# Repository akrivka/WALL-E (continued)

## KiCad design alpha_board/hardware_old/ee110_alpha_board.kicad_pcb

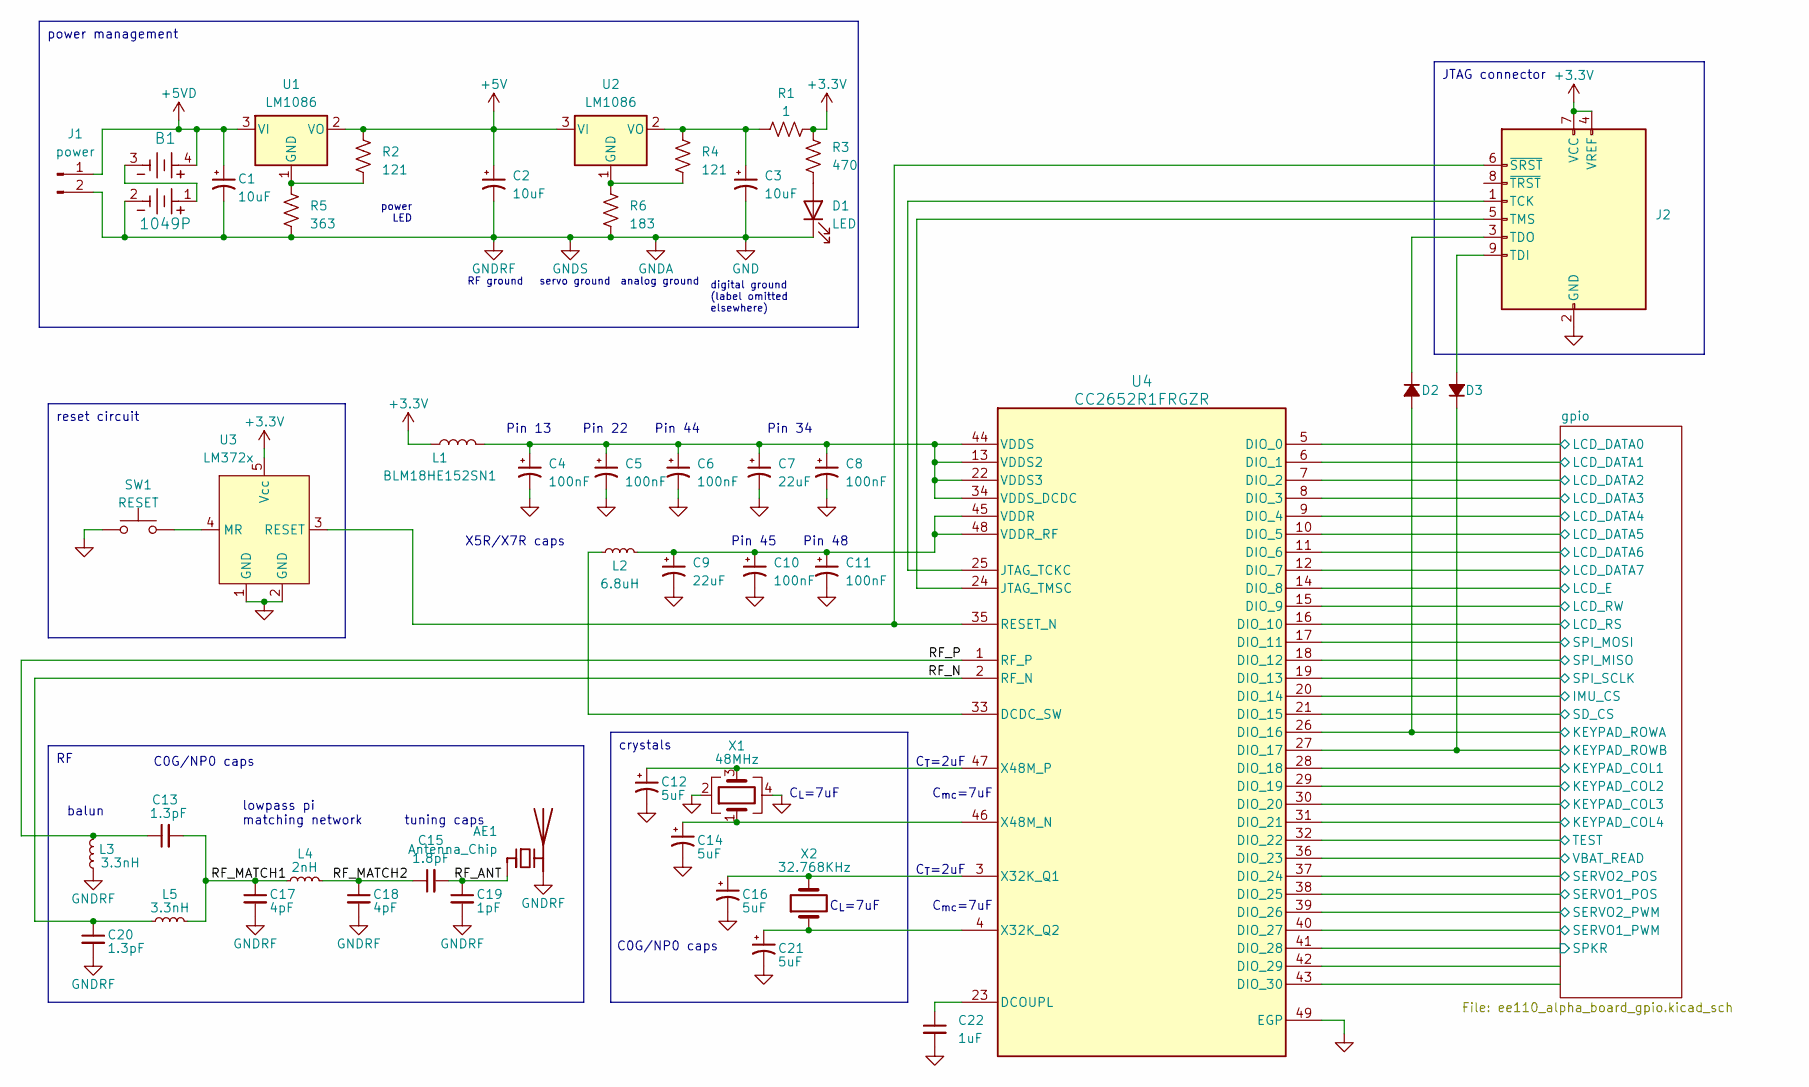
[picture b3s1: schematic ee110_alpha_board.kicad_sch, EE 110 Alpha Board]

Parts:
AE1: Antenna_Chip; EE110_Antenna
B1: 1049P; 1049P_KEY
C1, C2, C3: 10uF; CP_EIA-1608-08_AVX-J
C4, C5, C6, C8, C10, C11: 100nF; CP_EIA-1608-08_AVX-J
C7, C9: 22uF; CP_EIA-1608-08_AVX-J
C12, C14, C16, C21: 5uF; CP_EIA-1608-08_AVX-J
C13, C20: 1.3pF; C_1206_3216Metric
C15: 1.8pF; C_1206_3216Metric
C17, C18: 4pF; C_1206_3216Metric
C19: 1pF; C_1206_3216Metric
C22: 1uF; C_0603_1608Metric
D1: LED; LED_D3.0mm
D2, D3: D_Small_Filled; D_0603_1608Metric
J1: power; My_Power_Connector
J2: AVR-JTAG-10; CON10_2X5_DUK_FTSH_SAI
L1: BLM18HE152SN1; L_7.3x7.3_H3.5
L2: 6.8uH; L_0603_1608Metric
L3, L5: 3.3nH; L_1206_3216Metric
L4: 2nH; L_1206_3216Metric
R1: 1; R_0603_1608Metric
R2, R4: 121; R_0603_1608Metric
R3: 470; R_0603_1608Metric
R5: 363; R_0603_1608Metric
R6: 183; R_0603_1608Metric
SW1: RESET; SW_PUSH_6mm
U1, U2: LM1086; TO-263-3_TabPin2
U3: LM372x; SOT-23-5
U4: CC2652R1FRGZR; RGZ0048A_NV
X1: 48MHz; Crystal_SMD_2016-4Pin_2.0x1.6mm
X2: 32.768KHz; Crystal_SMD_3215-2Pin_3.2x1.5mm

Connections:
+3.3V: J2.4 (VREF), J2.7 (VCC), L1.1, R1.2, R3.1, U3.5 (Vcc); also elsewhere on the board
+5V: C2.1, R2.1, U1.2 (VO), U2.3 (VI); also elsewhere on the board
+5VD: B1.4, C1.1, J1.1, U1.3 (VI); also elsewhere on the board
/RF_ANT: AE1.1 (FEED), C15.2, C19.1
/RF_MATCH1: C13.2, C17.1, L4.1, L5.2
/RF_MATCH2: C15.1, C18.1, L4.2
/RF_N: C20.1, L5.1, U4.2 (RF_N)
/RF_P: C13.1, L3.2, U4.1 (RF_P)
/gpio/IMU_CS: U4.20 (DIO_14); also elsewhere on the board
/gpio/KEYPAD_COL1: U4.28 (DIO_18); also elsewhere on the board
/gpio/KEYPAD_COL2: U4.29 (DIO_19); also elsewhere on the board
/gpio/KEYPAD_COL3: U4.30 (DIO_20); also elsewhere on the board
/gpio/KEYPAD_COL4: U4.31 (DIO_21); also elsewhere on the board
/gpio/KEYPAD_ROWA: D2.2 (A), U4.26 (DIO_16); also elsewhere on the board
/gpio/KEYPAD_ROWB: D3.1 (K), U4.27 (DIO_17); also elsewhere on the board
/gpio/LCD_DATA0: U4.5 (DIO_0); also elsewhere on the board
/gpio/LCD_DATA1: U4.6 (DIO_1); also elsewhere on the board
/gpio/LCD_DATA2: U4.7 (DIO_2); also elsewhere on the board
/gpio/LCD_DATA3: U4.8 (DIO_3); also elsewhere on the board
/gpio/LCD_DATA4: U4.9 (DIO_4); also elsewhere on the board
/gpio/LCD_DATA5: U4.10 (DIO_5); also elsewhere on the board
/gpio/LCD_DATA6: U4.11 (DIO_6); also elsewhere on the board
/gpio/LCD_DATA7: U4.12 (DIO_7); also elsewhere on the board
/gpio/LCD_E: U4.14 (DIO_8); also elsewhere on the board
/gpio/LCD_RS: U4.16 (DIO_10); also elsewhere on the board
/gpio/LCD_RW: U4.15 (DIO_9); also elsewhere on the board
/gpio/SD_CS: U4.21 (DIO_15); also elsewhere on the board
/gpio/SERVO1_POS: U4.38 (DIO_25); also elsewhere on the board
/gpio/SERVO1_PWM: U4.40 (DIO_27); also elsewhere on the board
/gpio/SERVO2_POS: U4.37 (DIO_24); also elsewhere on the board
/gpio/SERVO2_PWM: U4.39 (DIO_26); also elsewhere on the board
/gpio/SPI_MISO: U4.18 (DIO_12); also elsewhere on the board
/gpio/SPI_MOSI: U4.17 (DIO_11); also elsewhere on the board
/gpio/SPI_SCLK: U4.19 (DIO_13); also elsewhere on the board
/gpio/SPKR: U4.41 (DIO_28); also elsewhere on the board
/gpio/TEST: U4.32 (DIO_22); also elsewhere on the board
/gpio/VBAT_READ: U4.36 (DIO_23); also elsewhere on the board
GND: AE1.2 (PCB_Trace), B1.2, C1.2, C2.2, C3.2, C4.2, C5.2, C6.2, C7.2, C8.2, C9.2, C10.2, C11.2, C12.2, C14.2, C16.2, C17.2, C18.2, C19.2, C20.2, C21.2, C22.2, D1.1 (K), J1.2, J2.2 (GND), J2.10 (GND), L3.1, R5.2, R6.2, SW1.1, U3.1 (GND), U3.2 (GND), U4.49 (EGP), X1.2, X1.4; also elsewhere on the board
unnamed: B1.1, B1.3
unnamed: D1.2 (A), R3.2
unnamed: D2.1 (K), J2.3 (TDO)
unnamed: D3.2 (A), J2.9 (TDI)
unnamed: J2.1 (TCK), U4.25 (JTAG_TCKC)
unnamed: J2.5 (TMS), U4.24 (JTAG_TMSC)
unnamed: J2.6 (~SRST), U3.3 (RESET), U4.35 (RESET_N)
unnamed: R2.2, R5.1, U1.1 (GND)
unnamed: R4.2, R6.1, U2.1 (GND)
unnamed: C3.1, R1.1, R4.1, U2.2 (VO)
unnamed: SW1.2, U3.4 (MR)
unnamed: L2.1, U4.33 (DCDC_SW)
unnamed: C22.1, U4.23 (DCOUPL)
unnamed: C9.1, C10.1, C11.1, L2.2, U4.45 (VDDR), U4.48 (VDDR_RF)
unnamed: C4.1, C5.1, C6.1, C7.1, C8.1, L1.2, U4.13 (VDDS2), U4.22 (VDDS3), U4.34 (VDDS_DCDC), U4.44 (VDDS)
unnamed: C16.1, U4.3 (X32K_Q1), X2.2
unnamed: C21.1, U4.4 (X32K_Q2), X2.1
unnamed: C14.1, U4.46 (X48M_N), X1.1
unnamed: C12.1, U4.47 (X48M_P), X1.3

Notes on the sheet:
reset circuit
power management
JTAG connector
crystals
Pin 22
power LED
C_{mc}=7uF
tuning caps
Pin 44
lowpass pi matching network
C0G/NP0 caps
X5R/X7R caps
C_{T}=2uF
RF ground
Pin 48
Pin 45
C_{L}=7uF
Pin 34
servo ground
analog ground
digital ground (label omitted elsewhere)
Pin 13
balun

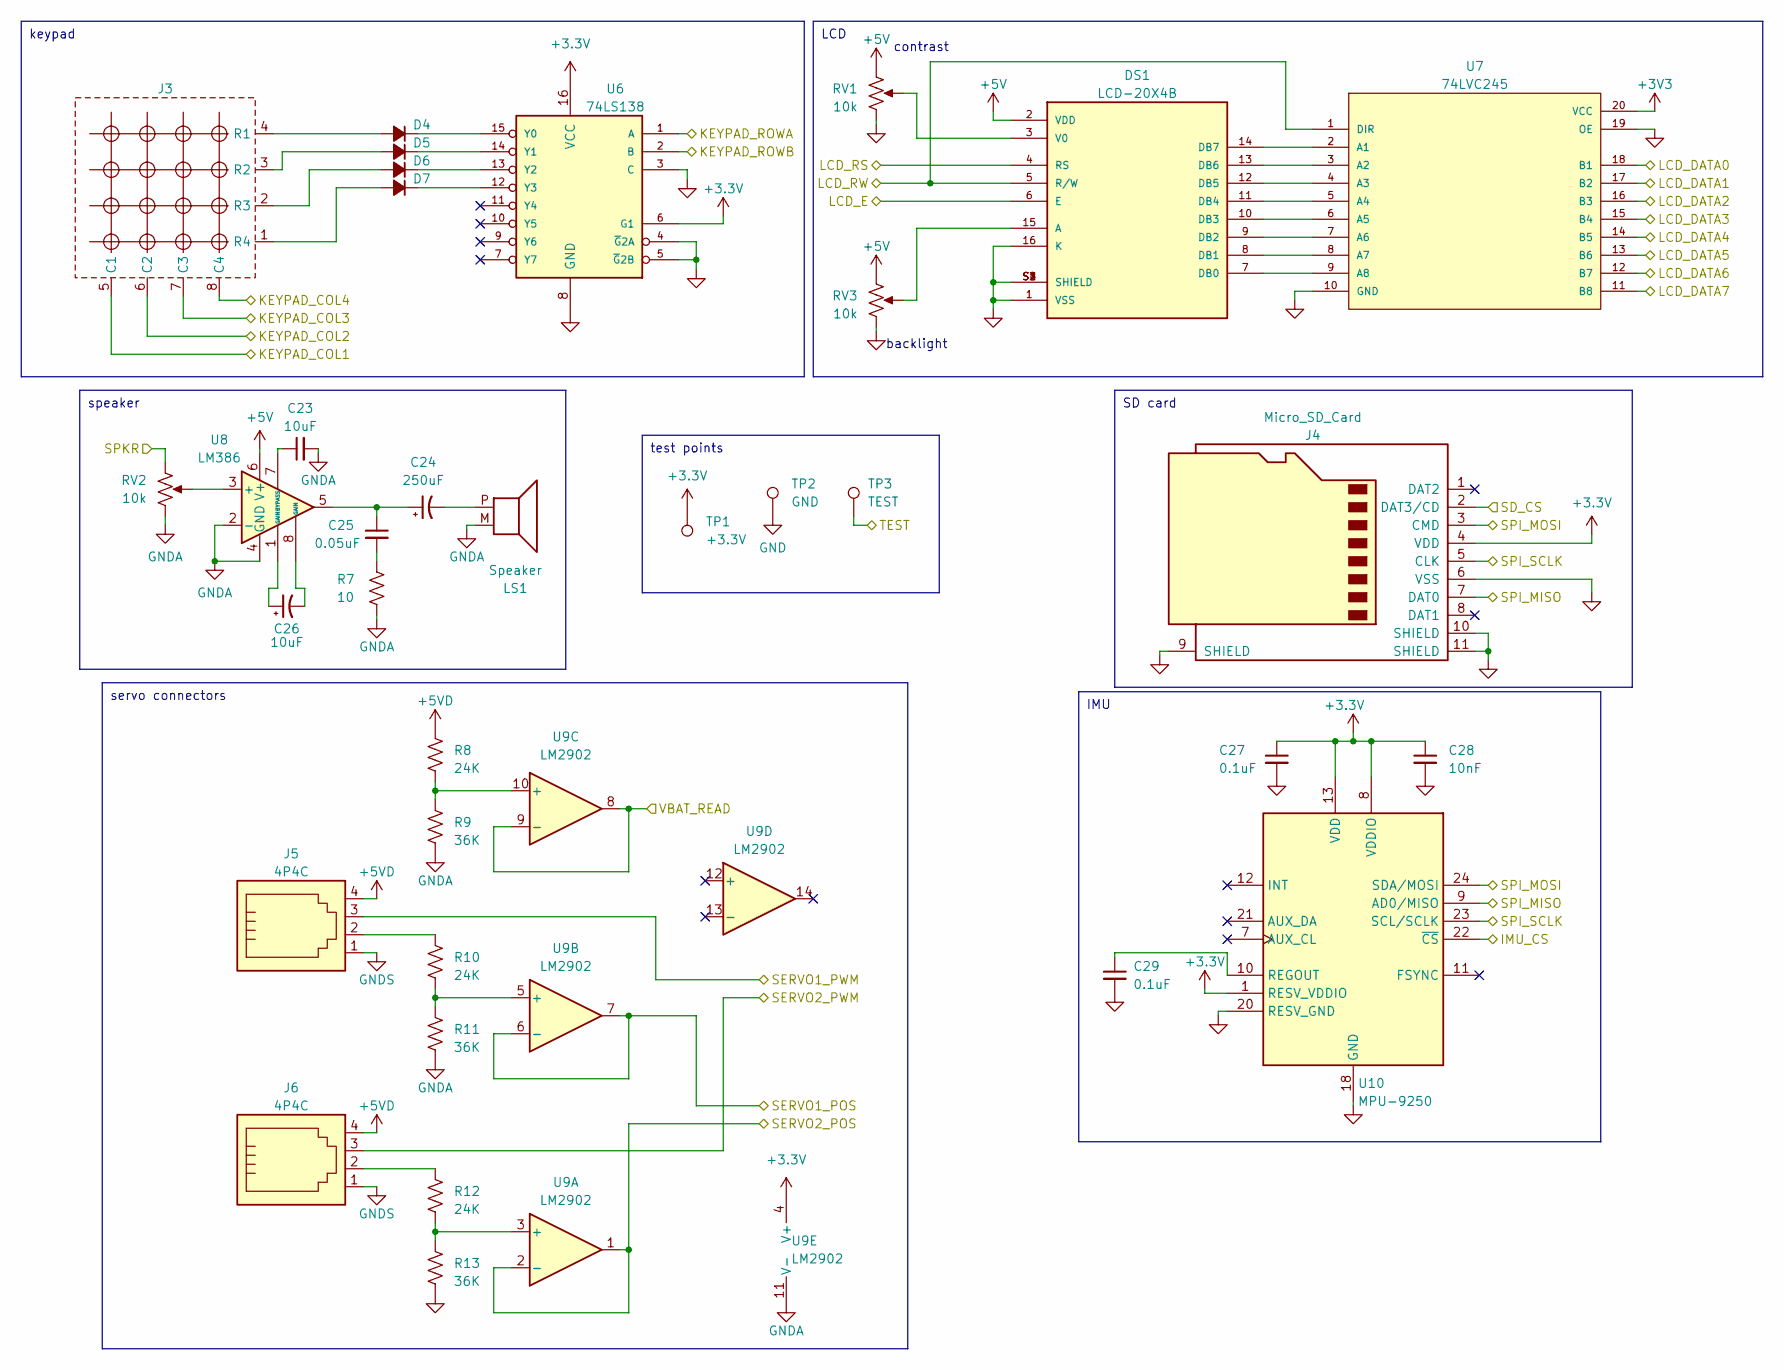
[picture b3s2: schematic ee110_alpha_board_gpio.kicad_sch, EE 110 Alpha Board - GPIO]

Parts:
C23, C26: 10uF; C_0603_1608Metric
C24: 250uF; C_0603_1608Metric
C25: 0.05uF; C_0603_1608Metric
C27, C29: 0.1uF; C_0603_1608Metric
C28: 10nF; C_0603_1608Metric
D4, D5, D6, D7: D_Small_Filled; D_0603_1608Metric
DS1: LCD-20X4B; LCD_LCD-20X4B; PARTREV N/A
J3: 4x4_Keypad
J4: Micro_SD_Card; microSD_HC_Hirose_DM3D-SF
J5, J6: 4P4C; JST_XH_S4B-XH-A-1_1x04_P2.50mm_Horizontal
LS1: Speaker; SPKR_CVS-1508
R7: 10; R_0603_1608Metric
R8, R10, R12: 24K; R_0603_1608Metric
R9, R11, R13: 36K; R_0603_1608Metric
RV1, RV3: 10k; Potentiometer_Bourns_3296P_Horizontal
RV2: 10k; TRIM_PTV09A-2015U-B103
TP1: +3.3V; TestPoint_THTPad_2.0x2.0mm_Drill1.0mm
TP2: GND; TestPoint_THTPad_2.0x2.0mm_Drill1.0mm
TP3: TEST; TestPoint_THTPad_2.0x2.0mm_Drill1.0mm
U6: 74LS138; SOIC-16_3.9x9.9mm_P1.27mm
U7: 74LVC245; SOIC-20W_7.5x15.4mm_P1.27mm
U8: LM386; DIP-8_W7.62mm
U9: LM2902; SOIC-14_3.9x8.7mm_P1.27mm
U10: MPU-9250; InvenSense_QFN-24_3x3mm_P0.4mm

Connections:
+3.3V: C27.1, C28.1, J4.4 (VDD), TP1.1, U6.6 (G1), U6.16 (VCC), U9.4 (V+), U10.1 (RESV_VDDIO), U10.8 (VDDIO), U10.13 (VDD); also elsewhere on the board
+3V3: U7.20 (VCC)
+5V: DS1.2 (VDD), RV1.1, RV3.1, U8.6 (V+); also elsewhere on the board
+5VD: J5.4, J6.4, R8.1; also elsewhere on the board
/gpio/IMU_CS: U10.22 (~CS); also elsewhere on the board
/gpio/KEYPAD_COL1: J3.5 (C1); also elsewhere on the board
/gpio/KEYPAD_COL2: J3.6 (C2); also elsewhere on the board
/gpio/KEYPAD_COL3: J3.7 (C3); also elsewhere on the board
/gpio/KEYPAD_COL4: J3.8 (C4); also elsewhere on the board
/gpio/KEYPAD_ROWA: U6.1 (A); also elsewhere on the board
/gpio/KEYPAD_ROWB: U6.2 (B); also elsewhere on the board
/gpio/LCD_DATA0: U7.18 (B1); also elsewhere on the board
/gpio/LCD_DATA1: U7.17 (B2); also elsewhere on the board
/gpio/LCD_DATA2: U7.16 (B3); also elsewhere on the board
/gpio/LCD_DATA3: U7.15 (B4); also elsewhere on the board
/gpio/LCD_DATA4: U7.14 (B5); also elsewhere on the board
/gpio/LCD_DATA5: U7.13 (B6); also elsewhere on the board
/gpio/LCD_DATA6: U7.12 (B7); also elsewhere on the board
/gpio/LCD_DATA7: U7.11 (B8); also elsewhere on the board
/gpio/LCD_E: DS1.6 (E); also elsewhere on the board
/gpio/LCD_RS: DS1.4 (RS); also elsewhere on the board
/gpio/LCD_RW: DS1.5 (R/W), U7.1 (DIR); also elsewhere on the board
/gpio/SD_CS: J4.2 (DAT3/CD); also elsewhere on the board
/gpio/SERVO1_POS: U9.6 (-), U9.7; also elsewhere on the board
/gpio/SERVO1_PWM: J5.3; also elsewhere on the board
/gpio/SERVO2_POS: U9.1, U9.2 (-); also elsewhere on the board
/gpio/SERVO2_PWM: J6.3; also elsewhere on the board
/gpio/SPI_MISO: J4.7 (DAT0), U10.9 (AD0/MISO); also elsewhere on the board
/gpio/SPI_MOSI: J4.3 (CMD), U10.24 (SDA/MOSI); also elsewhere on the board
/gpio/SPI_SCLK: J4.5 (CLK), U10.23 (SCL/SCLK); also elsewhere on the board
/gpio/SPKR: RV2.1; also elsewhere on the board
/gpio/TEST: TP3.1; also elsewhere on the board
/gpio/VBAT_READ: U9.8, U9.9 (-); also elsewhere on the board
GND: C23.2, C27.2, C28.2, C29.2, DS1.1 (VSS), DS1.16 (K), DS1.S1 (SHIELD), DS1.S2 (SHIELD), DS1.S3 (SHIELD), DS1.S4 (SHIELD), J4.6 (VSS), J4.9 (SHIELD), J4.10 (SHIELD), J4.11 (SHIELD), J5.1, J6.1, LS1.M (2), R7.2, R9.2, R11.2, R13.2, RV1.3, RV2.3, RV3.3, TP2.1, U6.3 (C), U6.4 (~G2A), U6.5 (~G2B), U6.8 (GND), U7.10 (GND), U7.19 (OE), U8.2 (-), U8.4 (GND), U9.11 (V-), U10.18 (GND), U10.20 (RESV_GND); also elsewhere on the board
unnamed: C24.1, C25.1, U8.5
unnamed: C25.2, R7.1
unnamed: C26.1, U8.1 (GAIN)
unnamed: C26.2, U8.8 (GAIN)
unnamed: D4.2 (A), J3.4 (R1)
unnamed: D4.1 (K), U6.15 (Y0)
unnamed: D5.2 (A), J3.3 (R2)
unnamed: D5.1 (K), U6.14 (Y1)
unnamed: D6.2 (A), J3.2 (R3)
unnamed: D6.1 (K), U6.13 (Y2)
unnamed: D7.2 (A), J3.1 (R4)
unnamed: D7.1 (K), U6.12 (Y3)
unnamed: DS1.15 (A), RV3.2
unnamed: DS1.7 (DB0), U7.9 (A8)
unnamed: DS1.8 (DB1), U7.8 (A7)
unnamed: DS1.9 (DB2), U7.7 (A6)
unnamed: DS1.10 (DB3), U7.6 (A5)
unnamed: DS1.11 (DB4), U7.5 (A4)
unnamed: DS1.12 (DB5), U7.4 (A3)
unnamed: DS1.13 (DB6), U7.3 (A2)
unnamed: DS1.14 (DB7), U7.2 (A1)
unnamed: DS1.3 (V0), RV1.2
unnamed: J5.2, R10.1
unnamed: J6.2, R12.1
unnamed: C24.2, LS1.P (1)
unnamed: RV2.2, U8.3 (+)
unnamed: C23.1, U8.7 (BYPASS)
unnamed: R12.2, R13.1, U9.3 (+)
unnamed: R10.2, R11.1, U9.5 (+)
unnamed: R8.2, R9.1, U9.10 (+)
unnamed: C29.1, U10.10 (REGOUT)

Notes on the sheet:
test points
keypad
SD card
servo connectors
speaker
LCD
IMU
backlight
contrast

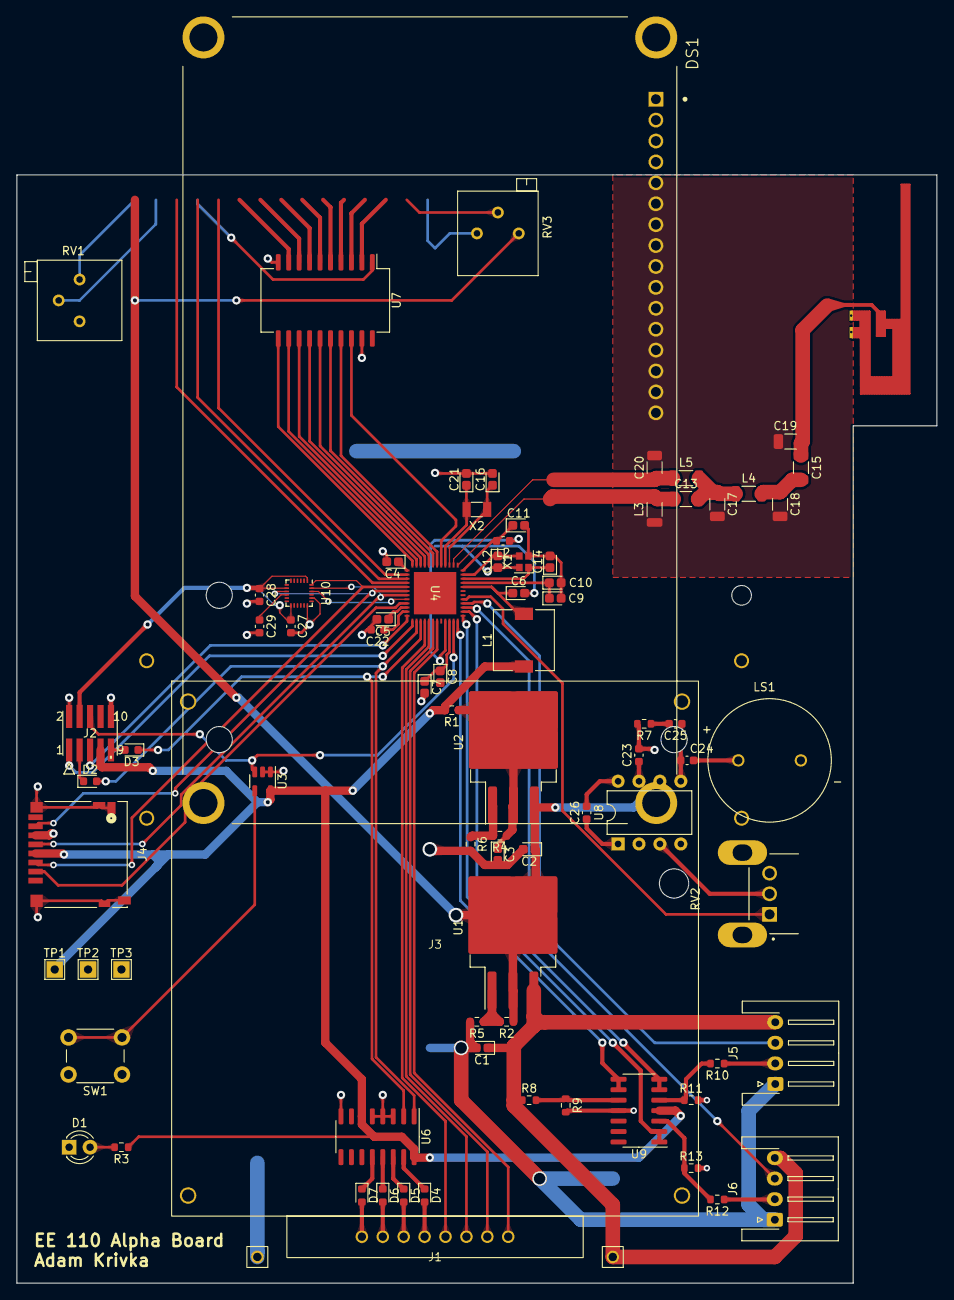
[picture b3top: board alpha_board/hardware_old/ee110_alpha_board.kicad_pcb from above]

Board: 2 copper layers, 111.8 x 134.6 mm, 82 parts (1 on the bottom side), 88 nets.

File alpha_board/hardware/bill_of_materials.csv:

"Id";"Designator";"Footprint";"Quantity";"Designation";"Supplier and ref";
1;"AE1";"EE110_Antenna";1;"Antenna_Chip";;;
2;"U8";"SOIC-14_3.9x8.7mm_P1.27mm";1;"LM2902";;;
3;"C17,C18";"C_1206_3216Metric_Pad1.33x1.80mm_HandSolder";2;"4pF";;;
4;"R10,R12,R14";"R_0603_1608Metric_Pad0.98x0.95mm_HandSolder";3;"24K";;;
5;"R15,R13,R11";"R_0603_1608Metric_Pad0.98x0.95mm_HandSolder";3;"36K";;;
6;"D10,D11";"D_1206_3216Metric_Pad1.42x1.75mm_HandSolder";2;"D_Small_Filled";;;
7;"C1,C3,C2";"CP_EIA-1608-08_AVX-J_Pad1.25x1.05mm_HandSolder";3;"10uF";;;
8;"C28";"C_0603_1608Metric_Pad1.08x0.95mm_HandSolder";1;"10nF";;;
9;"C12,C21,C16,C14";"CP_EIA-1608-08_AVX-J_Pad1.25x1.05mm_HandSolder";4;"5uF";;;
10;",,";"";3;"";;;
11;"C23,C26";"C_0603_1608Metric_Pad1.08x0.95mm_HandSolder";2;"10uF";;;
12;"U9";"QFN-24-1EP_3x3mm_P0.4mm_EP1.75x1.6mm";1;"MPU-9250";;;
13;"U6";"SOIC-20W_7.5x15.4mm_P1.27mm";1;"74LVC245";;;
14;"D7,D6,D4,D2,D5,D3";"D_0603_1608Metric_Pad1.05x0.95mm_HandSolder";6;"D_Small_Filled";;;
15;"C19";"C_1206_3216Metric_Pad1.33x1.80mm_HandSolder";1;"1pF";;;
16;"LS1";"SPKR_CVS-1508";1;"Speaker";;;
17;"C27,C29";"C_0603_1608Metric_Pad1.08x0.95mm_HandSolder";2;"0.1uF";;;
18;"D1";"LED_D3.0mm";1;"LED";;;
19;"C9,C7";"CP_EIA-1608-08_AVX-J_Pad1.25x1.05mm_HandSolder";2;"22uF";;;
20;"J3";"4x4_Keypad";1;"~";;;
21;"C15";"C_1206_3216Metric_Pad1.33x1.80mm_HandSolder";1;"1.8pF";;;
22;"RV2";"Potentiometer_Bourns_3296P_Horizontal";1;"1k";;;
23;"C4,C11,C8,C5,C10,C6";"CP_EIA-1608-08_AVX-J_Pad1.25x1.05mm_HandSolder";6;"100nF";;;
24;"J2";"CON10_2X5_DUK_FTSH_SAI";1;"AVR-JTAG-10";;;
25;"X1";"Crystal_SMD_2016-4Pin_2.0x1.6mm";1;"48MHz";;;
26;"R8,R4,R7";"R_0603_1608Metric_Pad0.98x0.95mm_HandSolder";3;"200";;;
27;"L5,L3";"L_1206_3216Metric_Pad1.22x1.90mm_HandSolder";2;"3.3nH";;;
28;"L2";"L_0603_1608Metric_Pad1.05x0.95mm_HandSolder";1;"6.8uH";;;
29;"RV3,RV1";"Potentiometer_Bourns_3296P_Horizontal";2;"10k";;;
30;"J6,J5";"JST_XH_S4B-XH-A-1_1x04_P2.50mm_Horizontal";2;"4P4C";;;
31;"L4";"L_1206_3216Metric_Pad1.22x1.90mm_HandSolder";1;"2nH";;;
32;"U2,U1";"TO-263-3_TabPin2";2;"LM1086";;;
33;"SW2";"SW_SPST_TL3342";1;"TEST_BUTTON";;;
34;"C24";"C_0603_1608Metric_Pad1.08x0.95mm_HandSolder";1;"250uF";;;
35;"U7";"DIP-8_W7.62mm";1;"LM386";;;
36;"TP1";"TestPoint_THTPad_2.0x2.0mm_Drill1.0mm";1;"TEST_BUTTON";;;
37;"TP2";"TestPoint_THTPad_2.0x2.0mm_Drill1.0mm";1;"TEST_GREEN";;;
38;"TP3";"TestPoint_THTPad_2.0x2.0mm_Drill1.0mm";1;"TEST_BLUE";;;
39;"R3,R2";"R_0603_1608Metric_Pad0.98x0.95mm_HandSolder";2;"121";;;
40;"SW1";"SW_SPST_TL3342";1;"RESET";;;
41;"DS1";"WINSTAR-WH1604A";1;"LCD-20X4B";;;
42;"TP5";"TestPoint_THTPad_2.0x2.0mm_Drill1.0mm";1;"GND";;;
43;"C25";"C_0603_1608Metric_Pad1.08x0.95mm_HandSolder";1;"0.05uF";;;
44;"TP4";"TestPoint_THTPad_2.0x2.0mm_Drill1.0mm";1;"+3.3V";;;
45;"U4";"RGZ0048A_NV";1;"CC2652R1FRGZR";;;
46;"R6";"R_0603_1608Metric_Pad0.98x0.95mm_HandSolder";1;"183";;;
47;"X2";"Crystal_SMD_3215-2Pin_3.2x1.5mm";1;"32.768KHz";;;
48;"C22";"C_0603_1608Metric_Pad1.08x0.95mm_HandSolder";1;"1uF";;;
49;"U5";"SOIC-16_3.9x9.9mm_P1.27mm";1;"74LS138";;;
50;"D8";"LED_0603_1608Metric_Pad1.05x0.95mm_HandSolder";1;"LED_GREEN";;;
51;"D9";"LED_0603_1608Metric_Pad1.05x0.95mm_HandSolder";1;"LED_BLUE";;;
52;"R1";"R_0603_1608Metric_Pad0.98x0.95mm_HandSolder";1;"100";;;
53;"R9";"R_0603_1608Metric_Pad0.98x0.95mm_HandSolder";1;"10";;;
54;"C20,C13";"C_1206_3216Metric_Pad1.33x1.80mm_HandSolder";2;"1.3pF";;;
55;"J4";"microSD_HC_Hirose_DM3D-SF";1;"Micro_SD_Card";;;
56;"R5";"R_0603_1608Metric_Pad0.98x0.95mm_HandSolder";1;"363";;;
57;"J1";"My_Power_Connector";1;"power";;;
58;"L1";"L_7.3x7.3_H3.5";1;"BLM18HE152SN1";;;
59;"U3";"SOT-23-5";1;"LM372x";;;
60;"B1";"1049P_KEY";1;"1049P";;;

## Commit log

2024-02-13 minor mistake to gitignore
2024-02-13 bruh
2024-02-13 added software
2024-02-13 added drawing sheet
2024-02-23 biig progress
2024-03-18 first revision
2024-04-08 Ilana committing from laptop
2024-04-15 alpha_board about to be sent out
2024-04-15 reorganized folders and started working on 3d print
2024-04-16 converted all parts to solidworks
2024-04-16 reorganized 3d_print folder
2024-04-16 finished scaling up all parts by 5/3
2024-04-16 improved 3d_print README
2024-04-20 uploaded new files
2024-04-21 arm assembly
2024-04-21 head assembly, TODO fix file names
2024-04-21 fixed errors in eyes
2024-04-21 Reorganized folders. Put repository in C/projects/ee110_robot if having issues
2024-04-24 flipped head part
2024-04-24 3d print progress
2024-04-25 wheel-spring+bearing
2024-04-26 reorganized folders a bit agaiiin, started alpha board revision 2
2024-04-27 split body-back, body-top and body-front into smaller parts
2024-04-27 split up into back-copy
2024-04-28 4/27
2024-04-28 neck almost done
2024-04-28 todo: fixes to neck
2024-05-05 ahh it's a mess
2024-05-05 neck done??
2024-05-18 much time has passed...
2024-05-20 asdf
2024-10-26 add remaining files
2024-10-27 Add soundeffects
2024-10-27 Add README and photos/video
2024-10-27 Crop first picture and fix video
2024-10-28 added the code and updated readme very slightly
